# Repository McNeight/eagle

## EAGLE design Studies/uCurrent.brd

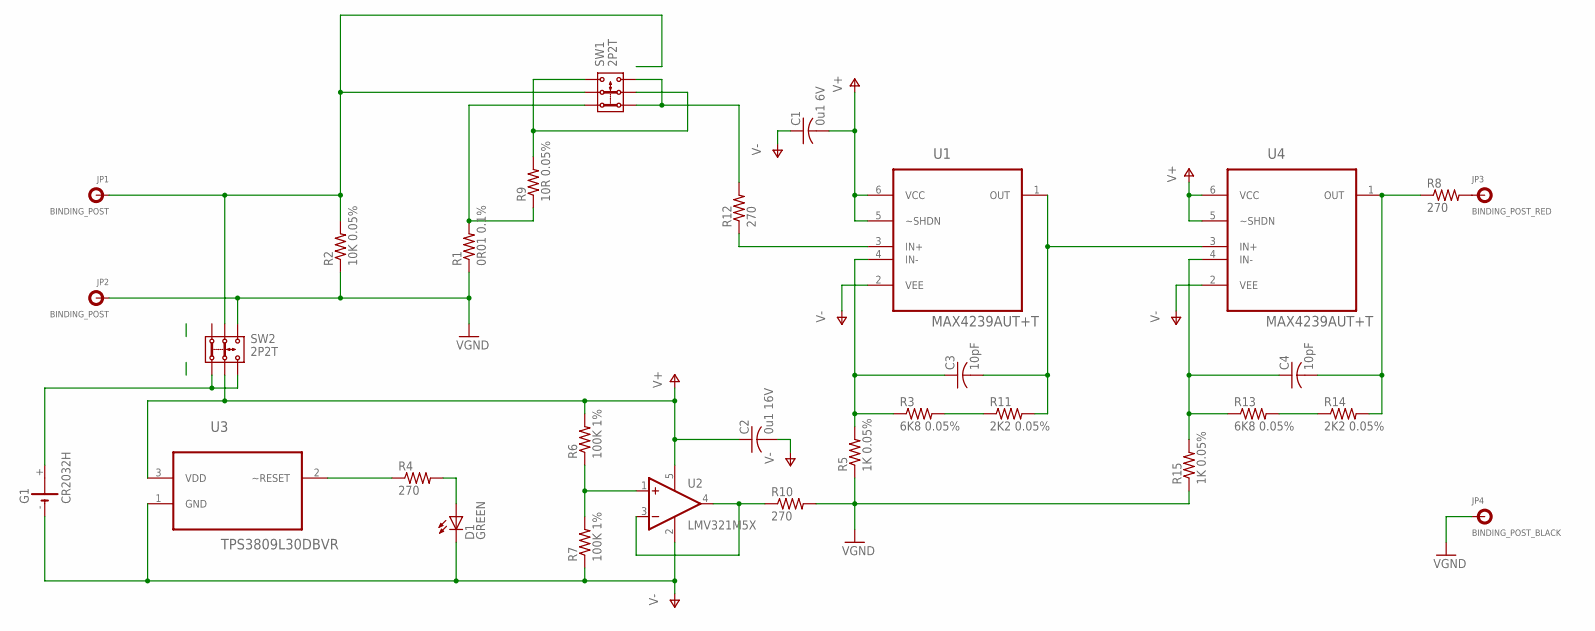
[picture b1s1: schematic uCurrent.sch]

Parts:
C1: 0u1 6V; C0402
C2: 0u1 16V; C0402
C3, C4: 10pF; C0402
D1: GREEN; LED3MM
G1: CR2032H
JP1, JP2: BINDING_POST
JP3: BINDING_POST_RED; BINDING_POST
JP4: BINDING_POST_BLACK; BINDING_POST
R1: 0R01 0.1%; R0402
R2: 10K 0.05%; R0402
R3, R13: 6K8 0.05%; R0402
R4, R8, R10, R12: 270; R0402
R5, R15: 1K 0.05%; R0402
R6, R7: 100K 1%; R0402
R9: 10R 0.05%; R0402
R11, R14: 2K2 0.05%; R0402
SW1, SW2: 2P2T
U1, U4: MAX4239AUT+T; SOT95P280X145-6N
U2: LMV321M5X; SOT23-5
U3: TPS3809L30DBVR; SOT95P280X145-3N

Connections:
unnamed: R4.1, U3.2 (~RESET)
unnamed: R6.1, R7.2, U2.1 (+IN)
unnamed: D1.A, R4.2
unnamed: R10.1, U2.3 (-IN), U2.4 (OUT)
unnamed: C3.2, R11.2, U1.1 (OUT), U4.3 (IN+)
unnamed: R3.2, R11.1
unnamed: C3.1, R3.1, R5.2, U1.4 (IN-)
unnamed: C4.2, R8.1, R14.2, U4.1 (OUT)
unnamed: R13.2, R14.1
unnamed: C4.1, R13.1, R15.2, U4.4 (IN-)
unnamed: R12.1, U1.3 (IN+)
unnamed: JP3.P$1, R8.2
unnamed: JP1.P$1, R2.2, SW1.2.1, SW2.2.1
unnamed: R1.2, R9.1, SW1.1.1
unnamed: G1.+, SW2.1.2, SW2.3.2
unnamed: R12.2, SW1.1.2, SW1.3.2
unnamed: R9.2, SW1.2.2, SW1.3.1
V+: C1.2, C2.1, R6.2, SW2.2.2, U1.5 (~SHDN), U1.6 (VCC), U2.5 (V+), U3.3 (VDD), U4.5 (~SHDN), U4.6 (VCC)
V-: C1.1, C2.2, D1.K (C), G1.-, R7.1, U1.2 (VEE), U2.2 (V-), U3.1 (GND), U4.2 (VEE)
VGND: JP2.P$1, JP4.P$1, R1.1, R2.1, R5.1, R10.2, R15.1, SW2.3.1

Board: 2 copper layers, 31 parts (0 on the bottom side), 20 nets, no tracks yet.

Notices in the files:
parts and their libraries:
SparkFun-Connectors: Licensing: Creative Commons ShareAlike 4.0 International - https://creativecommons.org/licenses/by-sa/4.0
